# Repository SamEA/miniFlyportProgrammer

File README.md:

miniFlyportProgrammer
=====================

A mini USB Programmer/Expansion Board for Flyport

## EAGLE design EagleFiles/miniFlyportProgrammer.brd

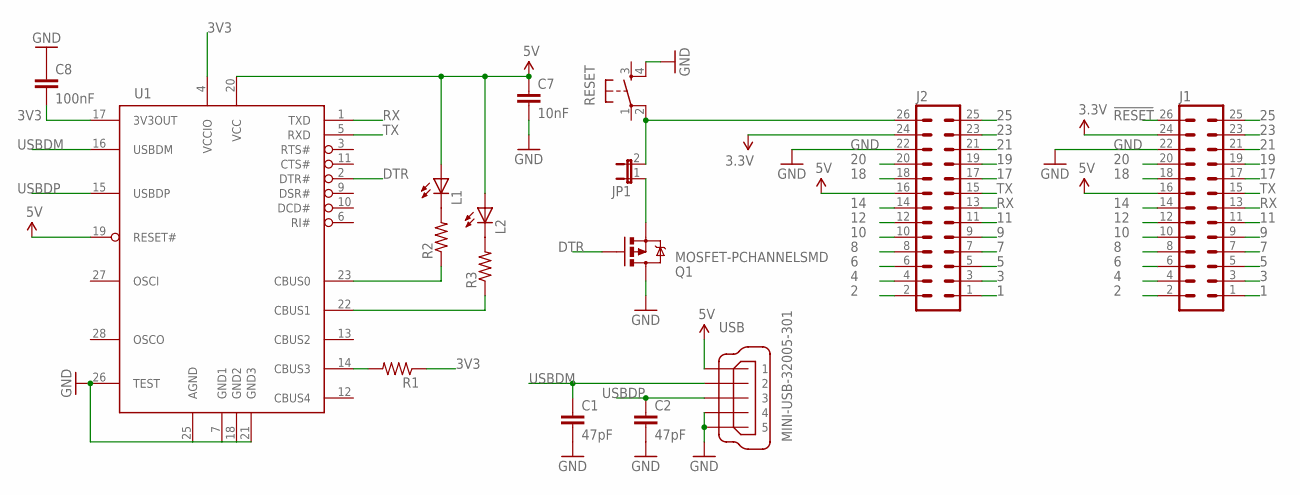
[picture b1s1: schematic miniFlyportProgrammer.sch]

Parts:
C1, C2: 47pF; C0603
C7: 10nF; C0603
C8: 100nF; C0603
J1, J2: MA13-2
JP1: JUMPER-2PTH; 1X02
L1, L2: LED0603; LED-0603
Q1: MOSFET-PCHANNELSMD; SOT23-3
R1, R2, R3: RESISTOR0603-RES; 0603-RES
RESET: TAC_SWITCHSMD; TACTILE_SWITCH_SMD
U1: FT232RL; SSOP28DB
USB: MINI-USB-32005-301; 32005-301

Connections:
1: J1.1, J2.1
2: J1.2, J2.2
3: J1.3, J2.3
3.3V: J1.24, J2.24
3V3: C8.2, R1.1, U1.4 (VCCIO), U1.17 (3V3OUT)
4: J1.4, J2.4
5: J1.5, J2.5
5V: C7.1, J1.16, J2.16, L1.A, L2.A, U1.19 (RESET#), U1.20 (VCC), USB.1
6: J1.6, J2.6
7: J1.7, J2.7
8: J1.8, J2.8
9: J1.9, J2.9
10: J1.10, J2.10
11: J1.11, J2.11
12: J1.12, J2.12
14: J1.14, J2.14
17: J1.17, J2.17
18: J1.18, J2.18
19: J1.19, J2.19
20: J1.20, J2.20
21: J1.21, J2.21
23: J1.23, J2.23
25: J1.25, J2.25
!RESET: J1.26, J2.26, JP1.2, RESET.2
DTR: Q1.1 (G), U1.2 (DTR#)
GND: C1.2, C2.2, C7.2, C8.1, J1.22, J2.22, Q1.3 (D), RESET.4, U1.7 (GND1), U1.18 (GND2), U1.21 (GND3), U1.25 (AGND), U1.26 (TEST), USB.4, USB.5
unnamed: JP1.1, Q1.2 (S)
unnamed: L1.C, R2.2
unnamed: L2.C, R3.2
unnamed: R1.2, U1.14 (CBUS3)
unnamed: R2.1, U1.23 (CBUS0)
unnamed: R3.1, U1.22 (CBUS1)
RX: J1.13, J2.13, U1.1 (TXD)
TX: J1.15, J2.15, U1.5 (RXD)
USBDM: C1.1, U1.16 (USBDM), USB.2
USBDP: C2.1, U1.15 (USBDP), USB.3

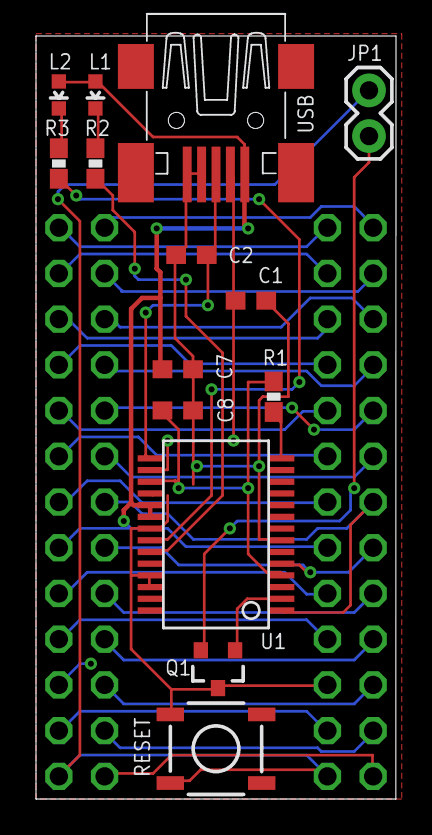
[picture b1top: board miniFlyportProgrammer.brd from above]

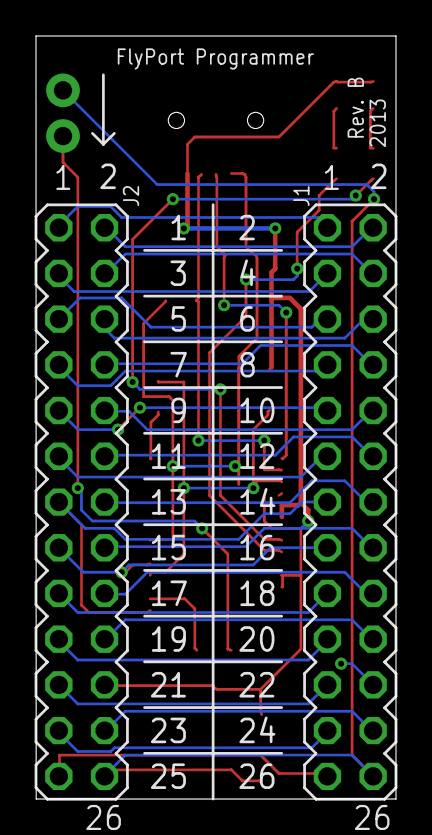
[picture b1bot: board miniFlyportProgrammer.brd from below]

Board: 2 copper layers, 20.0 x 42.4 mm, 16 parts (2 on the bottom side), 36 nets.

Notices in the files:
parts and their libraries:
SparkFun-LED: Licensing: CC v3.0 Share-Alike You are welcome to use this library for commercial purposes.
